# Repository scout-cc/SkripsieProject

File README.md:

# SkripsieProject
Designs and reports for personal final year engineering project

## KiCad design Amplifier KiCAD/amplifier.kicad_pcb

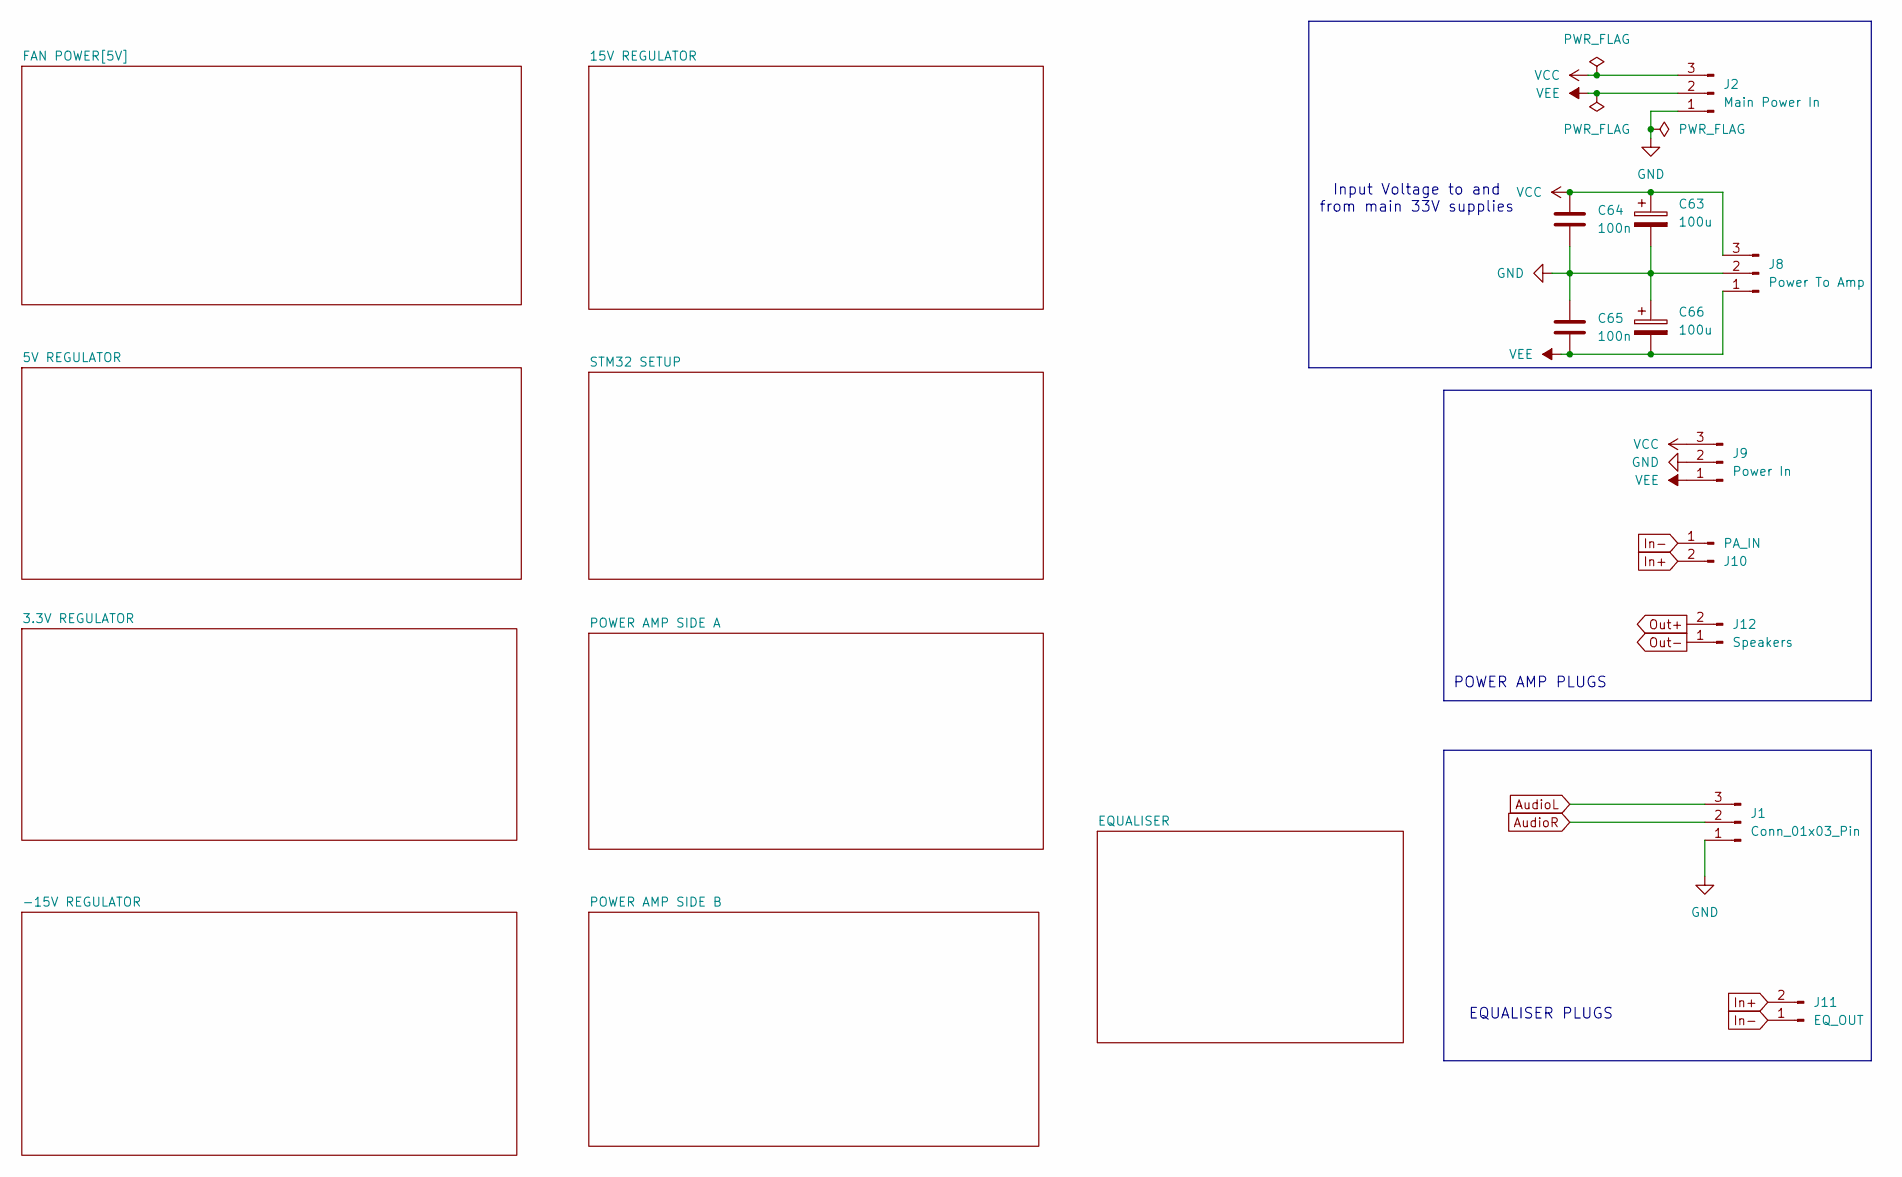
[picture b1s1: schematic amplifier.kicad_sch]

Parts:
C63, C66: 100u; CP_Radial_D6.3mm_P2.50mm
C64, C65: 100n; C_Rect_L7.2mm_W2.5mm_P5.00mm
J1: Conn_01x03_Pin; CUI_SJ1-3513
J2: Main Power In; PHOENIX_1829167
J8: Power To Amp; PHOENIX_1829167
J9: Power In; PHOENIX_1829167
J10: PA_IN; JST_PH_B3B-PH-K_1x03_P2.00mm_Vertical
J11: EQ_OUT; JST_PH_B3B-PH-K_1x03_P2.00mm_Vertical
J12: Speakers; PHOENIX_1757242

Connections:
AudioL: J1.3; also elsewhere on the board
AudioR: J1.2; also elsewhere on the board
GND: C63.2, C64.1, C65.2, C66.1, J1.1, J2.1, J8.2, J9.2; also elsewhere on the board
In+: J10.2, J11.2; also elsewhere on the board
In-: J10.1, J11.1; also elsewhere on the board
Out+: J12.2; also elsewhere on the board
Out-: J12.1; also elsewhere on the board
VCC: C63.1, C64.2, J2.3, J8.3, J9.3; also elsewhere on the board
VEE: C65.1, C66.2, J2.2, J8.1, J9.1; also elsewhere on the board

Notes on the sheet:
EQUALISER PLUGS
Input Voltage to and from main 33V supplies
POWER AMP PLUGS

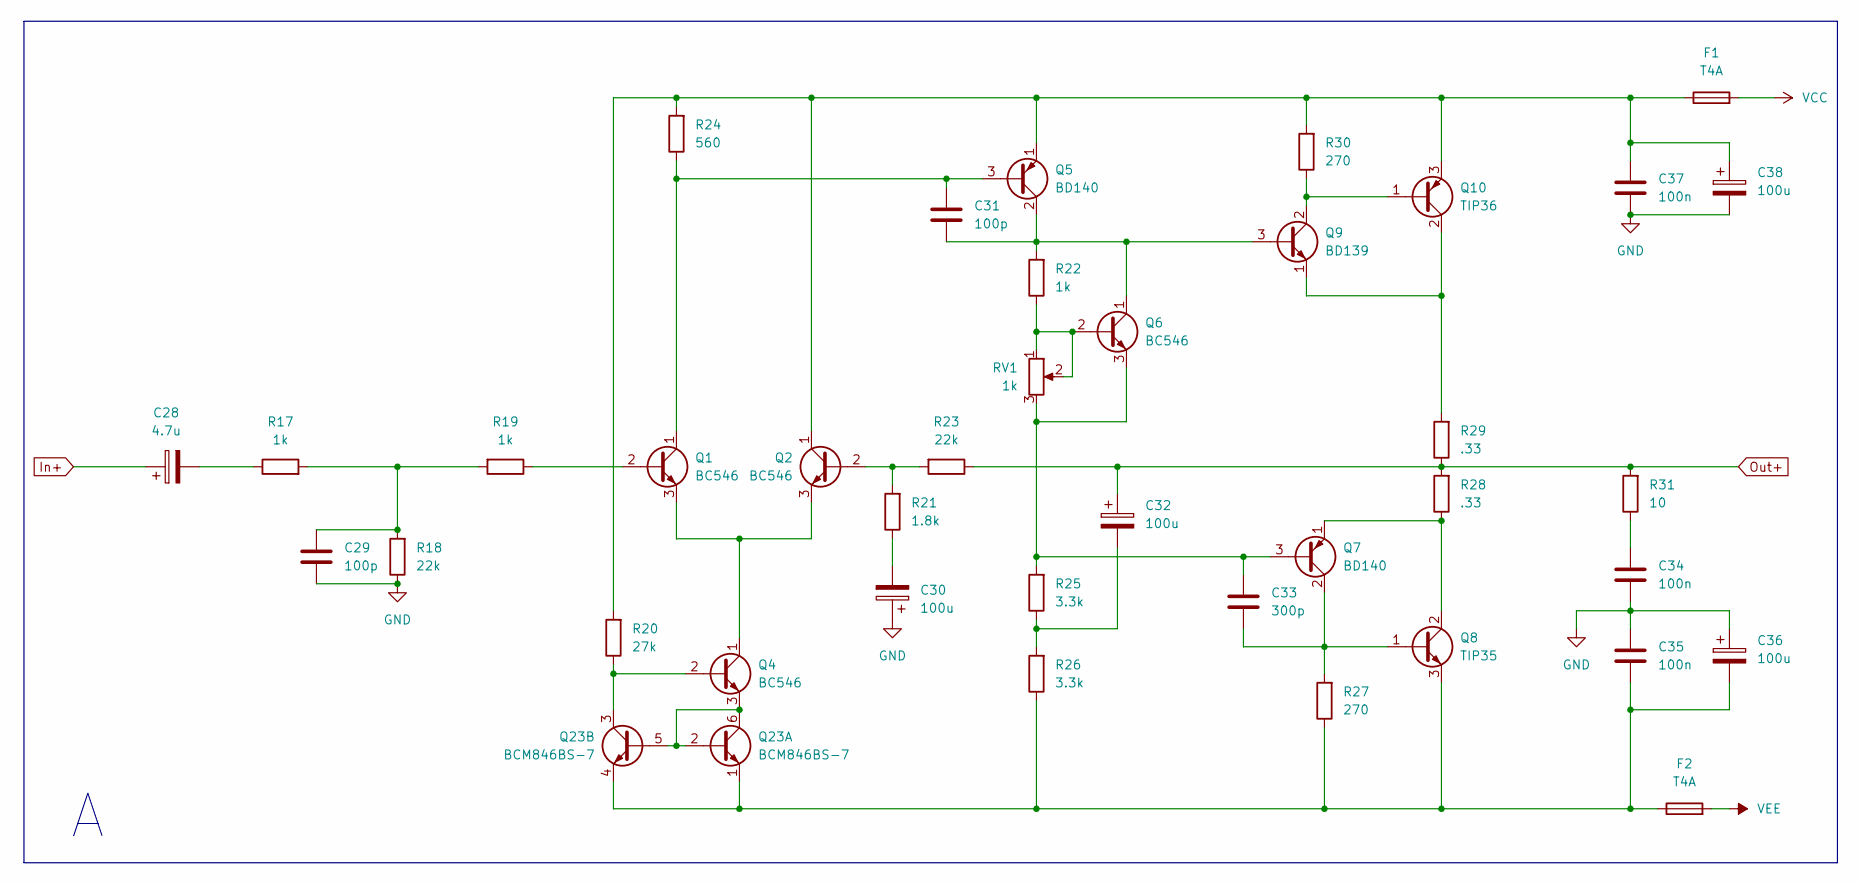
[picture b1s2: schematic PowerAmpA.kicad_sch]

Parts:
C28: 4.7u; GCJ31CC71H475KA01L
C29, C31: 100p; C0805C101J5GACTU
C30, C32, C36, C38: 100u; CP_Radial_D6.3mm_P2.50mm
C33: 300p; C0805C301J5GACTU
C34, C35, C37: 100n; C_Rect_L7.2mm_W2.5mm_P5.00mm
F1, F2: T4A; Fuseholder_Cylinder-5x20mm_Schurter_0031_8201_Horizontal_Op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
Q1, Q2, Q4, Q6: BC546; TO-92_Inline
Q5, Q7: BD140; TO-126-3_Vertical
Q8: TIP35; TO-247-3_Horizontal_TabDown
Q9: BD139; TO-126-3_Vertical
Q10: TIP36; TO-247-3_Horizontal_TabDown
Q23: BCM846BS-7; SOT-363_SC-70-6
R17, R19, R22: 1k; R_Axial_DIN0207_L6.3mm_D2.5mm_P10.16mm_Horizontal
R18, R23: 22k; R_Axial_DIN0207_L6.3mm_D2.5mm_P10.16mm_Horizontal
R20: 27k; R_Axial_DIN0207_L6.3mm_D2.5mm_P10.16mm_Horizontal
R21: 1.8k; R_Axial_DIN0207_L6.3mm_D2.5mm_P10.16mm_Horizontal
R24: 560; R_Axial_DIN0207_L6.3mm_D2.5mm_P10.16mm_Horizontal
R25, R26: 3.3k; R_Axial_DIN0207_L6.3mm_D2.5mm_P10.16mm_Horizontal
R27, R30: 270; R_Axial_DIN0207_L6.3mm_D2.5mm_P10.16mm_Horizontal
R28, R29: .33; R_Box_L26.0mm_W5.0mm_P20.00mm
R31: 10; R_Axial_DIN0411_L9.9mm_D3.6mm_P15.24mm_Horizontal
RV1: 1k; Potentiometer_Bourns_3296W_Vertical

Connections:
GND: C29.1, C30.1, C34.1, C35.2, C36.1, C37.1, C38.2, R18.1; also elsewhere on the board
In+: C28.1; also elsewhere on the board
unnamed: C28.2, R17.1
unnamed: C29.2, R17.2, R18.2, R19.2
unnamed: C30.2, R21.1
unnamed: C32.2, R25.1, R26.2
unnamed: C34.2, R31.1
unnamed: Q1.2 (B), R19.1
unnamed: C31.2, Q1.1 (C), Q5.3 (B), R24.1
unnamed: Q1.3 (E), Q2.3 (E), Q4.1 (C)
unnamed: Q2.2 (B), R21.2, R23.2
unnamed: C31.1, Q5.2 (C), Q6.1 (C), Q9.3 (B), R22.2
unnamed: Q6.2 (B), R22.1, RV1.1, RV1.2
unnamed: C33.2, Q6.3 (E), Q7.3 (B), R25.2, RV1.3
unnamed: C33.1, Q7.2 (C), Q8.1 (B), R27.2
unnamed: Q7.1 (E), Q8.2 (C), R28.1
unnamed: Q9.2 (C), Q10.1 (B), R30.1
unnamed: Q9.1 (E), Q10.2 (C), R29.2
unnamed: C37.2, C38.1, F1.1, Q2.1 (C), Q5.1 (E), Q10.3 (E), R20.2, R24.2, R30.2
unnamed: Q4.3 (E), Q23.2 (B1), Q23.5 (B2), Q23.6 (C1)
unnamed: C35.1, C36.2, F2.1, Q8.3 (E), Q23.1 (E1), Q23.4 (E2), R26.1, R27.1
unnamed: Q4.2 (B), Q23.3 (C2), R20.1
Out+: C32.1, R23.1, R28.2, R29.1, R31.2; also elsewhere on the board
VCC: F1.2; also elsewhere on the board
VEE: F2.2; also elsewhere on the board

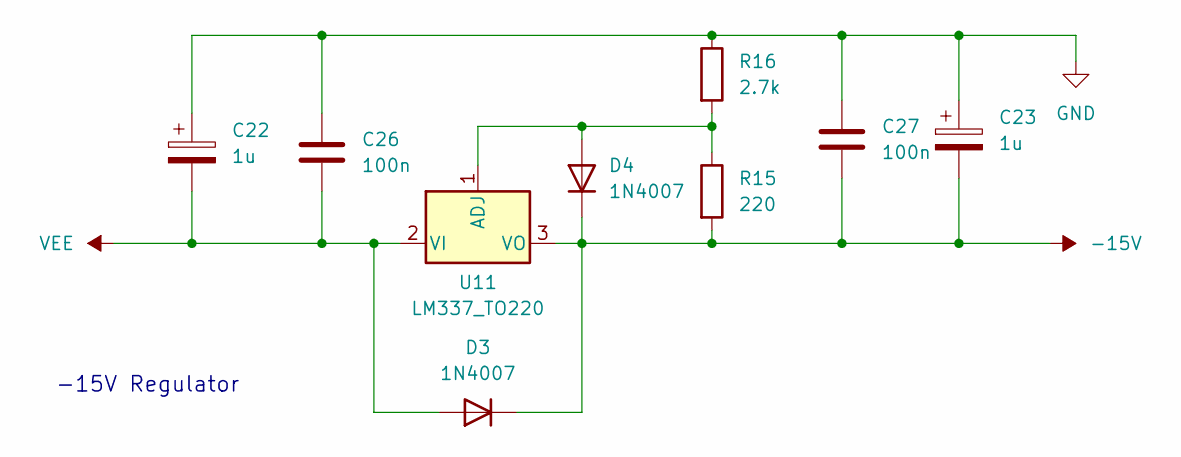
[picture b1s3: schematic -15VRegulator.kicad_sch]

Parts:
C22, C23: 1u; GJ821BR71H105KA12L
C26, C27: 100n; C_Rect_L7.2mm_W2.5mm_P5.00mm
D3, D4: 1N4007; D_DO-41_SOD81_P10.16mm_Horizontal
R15: 220; R_Axial_DIN0207_L6.3mm_D2.5mm_P10.16mm_Horizontal
R16: 2.7k; R_Axial_DIN0207_L6.3mm_D2.5mm_P10.16mm_Horizontal
U11: LM337_TO220; TO-220-3_Horizontal_TabDown

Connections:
-15V: C23.2, C27.2, D3.1 (K), D4.1 (K), R15.2, U11.3 (VO); also elsewhere on the board
GND: C22.1, C23.1, C26.1, C27.1, R16.1; also elsewhere on the board
unnamed: D4.2 (A), R15.1, R16.2, U11.1 (ADJ)
VEE: C22.2, C26.2, D3.2 (A), U11.2 (VI); also elsewhere on the board

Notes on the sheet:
-15V Regulator

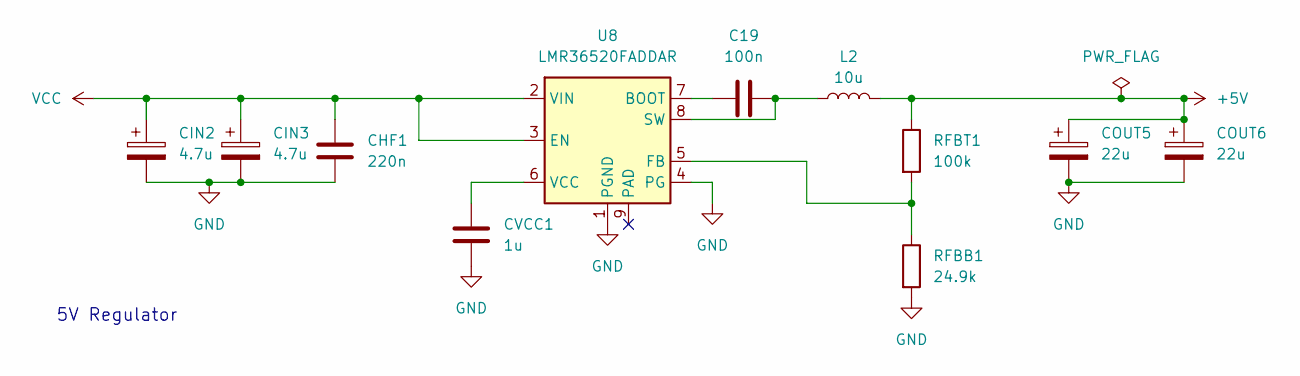
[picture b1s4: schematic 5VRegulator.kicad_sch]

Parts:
C19: 100n; C_Rect_L7.2mm_W2.5mm_P5.00mm
CHF1: 220n; C_Rect_L7.2mm_W2.5mm_P5.00mm
CIN2, CIN3: 4.7u; GCJ31CC71H475KA01L
COUT5, COUT6: 22u; G-32_MUR
CVCC1: 1u; GJ821BR71H105KA12L
L2: 10u; IND_SRP1038A_BRN
RFBB1: 24.9k; R_0805_2012Metric
RFBT1: 100k; R_Axial_DIN0207_L6.3mm_D2.5mm_P10.16mm_Horizontal
U8: LMR36520FADDAR; Texas_HTSOP-8-1EP_3.9x4.9mm_P1.27mm_EP2.95x4.9mm_Mask2.4x3.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

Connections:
+5V: COUT5.1, COUT6.1, L2.2, RFBT1.1; also elsewhere on the board
GND: CHF1.2, CIN2.2, CIN3.2, COUT5.2, COUT6.2, CVCC1.2, RFBB1.2, U8.1 (PGND), U8.4 (PG); also elsewhere on the board
unnamed: C19.1, U8.7 (BOOT)
unnamed: RFBB1.1, RFBT1.2, U8.5 (FB)
unnamed: C19.2, L2.1, U8.8 (SW)
unnamed: CVCC1.1, U8.6 (VCC)
VCC: CHF1.1, CIN2.1, CIN3.1, U8.2 (VIN), U8.3 (EN); also elsewhere on the board

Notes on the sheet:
5V Regulator

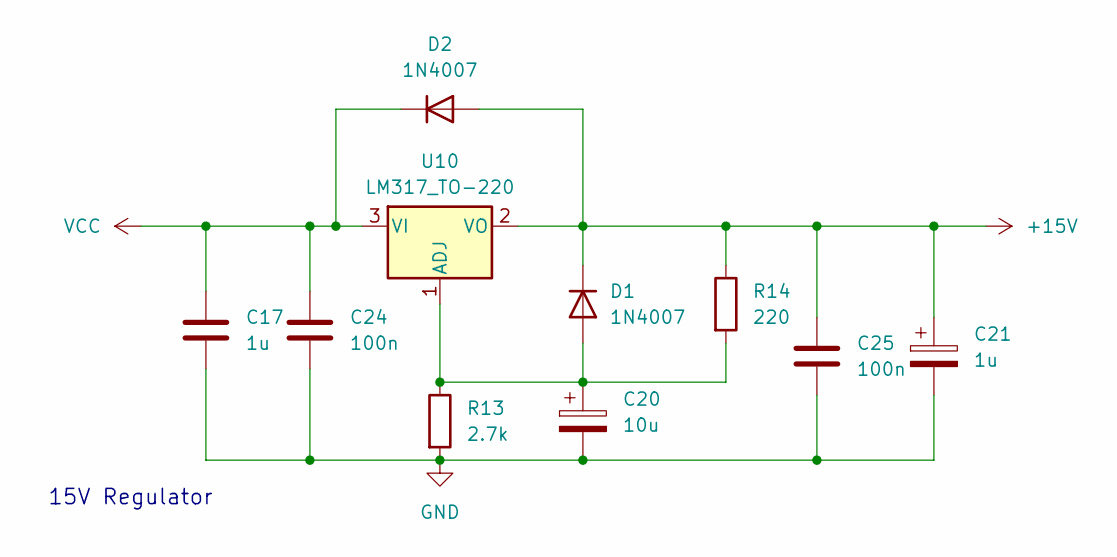
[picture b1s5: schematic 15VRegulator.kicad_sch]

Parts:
C17, C21: 1u; GJ821BR71H105KA12L
C20: 10u; CAP_GCM32_MUR
C24, C25: 100n; C_Rect_L7.2mm_W2.5mm_P5.00mm
D1, D2: 1N4007; D_DO-41_SOD81_P10.16mm_Horizontal
R13: 2.7k; R_Axial_DIN0207_L6.3mm_D2.5mm_P10.16mm_Horizontal
R14: 220; R_Axial_DIN0207_L6.3mm_D2.5mm_P10.16mm_Horizontal
U10: LM317_TO-220; TO-220-3_Horizontal_TabDown

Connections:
+15V: C21.1, C25.1, D1.1 (K), D2.2 (A), R14.1, U10.2 (VO); also elsewhere on the board
GND: C17.2, C20.2, C21.2, C24.2, C25.2, R13.2; also elsewhere on the board
unnamed: C20.1, D1.2 (A), R13.1, R14.2, U10.1 (ADJ)
VCC: C17.1, C24.1, D2.1 (K), U10.3 (VI); also elsewhere on the board

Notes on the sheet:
15V Regulator

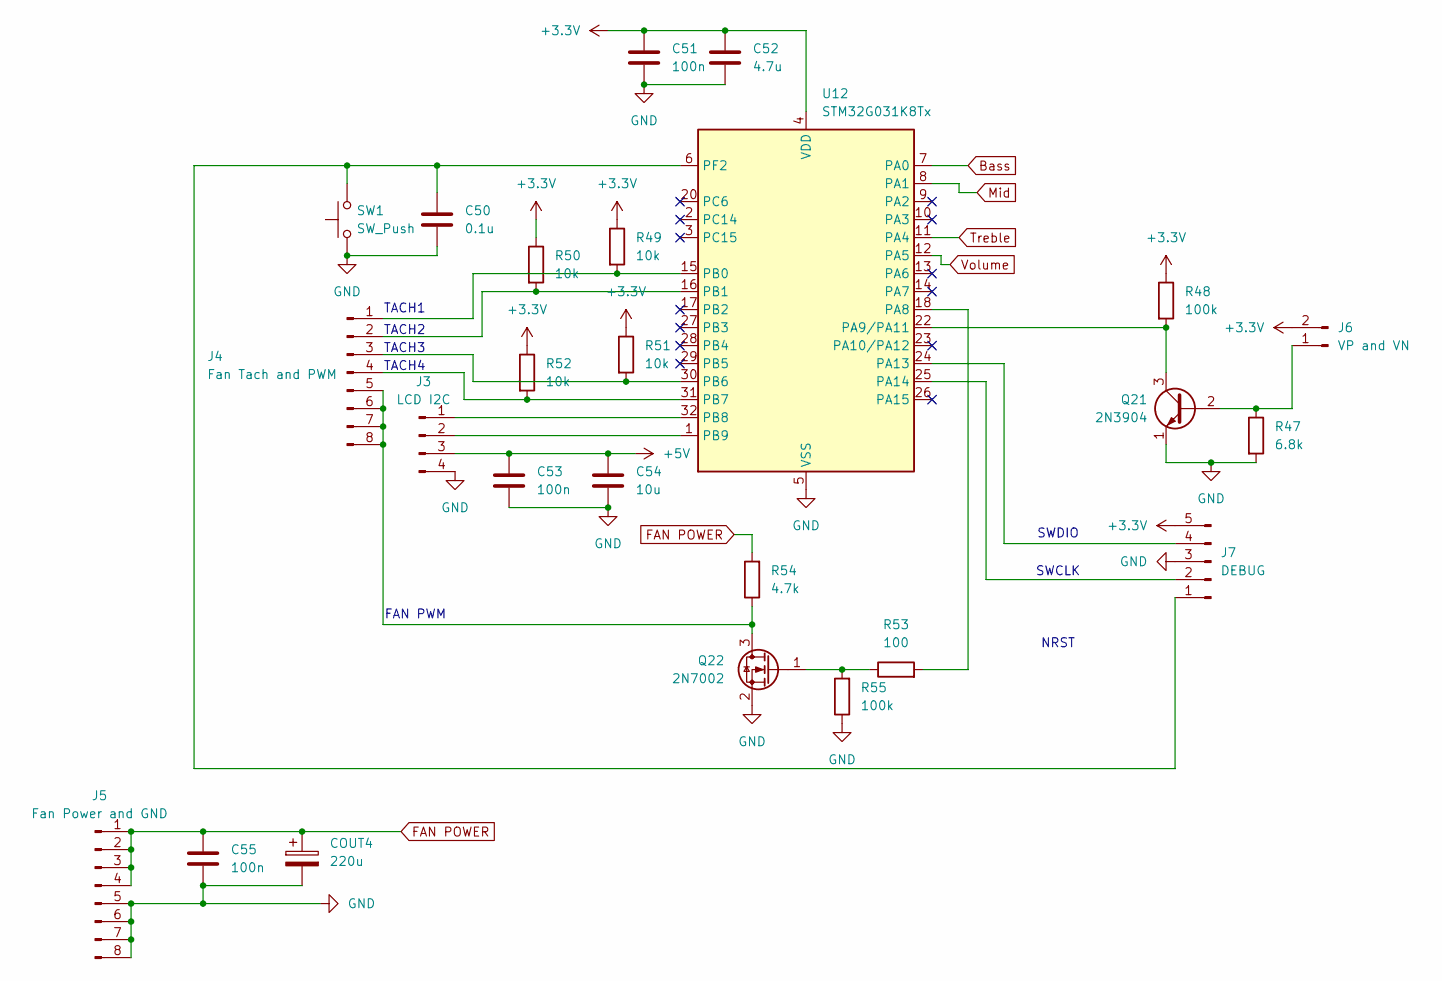
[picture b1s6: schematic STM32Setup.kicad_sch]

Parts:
C50: 0.1u; C_Rect_L7.2mm_W2.5mm_P5.00mm
C51, C53, C55: 100n; C_Rect_L7.2mm_W2.5mm_P5.00mm
C52: 4.7u; GCJ31CC71H475KA01L
C54: 10u; CAP_GCM32_MUR
COUT4: 220u; CP_Radial_D6.3mm_P2.50mm
J3: LCD I2C; PinHeader_1x04_P2.00mm_Vertical
J4: Fan Tach and PWM; JST_XH_B8B-XH-A_1x08_P2.50mm_Vertical
J5: Fan Power and GND; Molex_Micro-Fit_3.0_43045-0812_2x04_P3.00mm_Vertical
J6: VP and VN; JST_PH_B2B-PH-K_1x02_P2.00mm_Vertical
J7: DEBUG; JST_PH_B5B-PH-K_1x05_P2.00mm_Vertical
Q21: 2N3904; TO-92_Inline
Q22: 2N7002; SOT-23
R47: 6.8k; R_Axial_DIN0207_L6.3mm_D2.5mm_P10.16mm_Horizontal
R48, R55: 100k; R_Axial_DIN0207_L6.3mm_D2.5mm_P10.16mm_Horizontal
R49, R50, R51, R52: 10k; R_Axial_DIN0207_L6.3mm_D2.5mm_P10.16mm_Horizontal
R53: 100; R_Axial_DIN0207_L6.3mm_D2.5mm_P10.16mm_Horizontal
R54: 4.7k; R_Axial_DIN0207_L6.3mm_D2.5mm_P10.16mm_Horizontal
SW1: SW_Push; SW_PUSH_6mm_H5mm
U12: STM32G031K8Tx; LQFP-32_7x7mm_P0.8mm

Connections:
+3.3V: C51.1, C52.1, J6.2, J7.5, R48.1, R49.1, R50.1, R51.1, R52.1, U12.4 (VDD); also elsewhere on the board
+5V: C53.1, C54.1, J3.3; also elsewhere on the board
Bass: U12.7 (PA0); also elsewhere on the board
FAN POWER: C55.1, COUT4.1, J5.1, J5.2, J5.3, J5.4, R54.2; also elsewhere on the board
GND: C50.2, C51.2, C52.2, C53.2, C54.2, C55.2, COUT4.2, J3.4, J5.5, J5.6, J5.7, J5.8, J7.3, Q21.1 (E), Q22.2 (S), R47.2, R55.1, SW1.1, U12.5 (VSS); also elsewhere on the board
Mid: U12.8 (PA1); also elsewhere on the board
unnamed: J3.1, U12.32 (PB8)
unnamed: J3.2, U12.1 (PB9)
unnamed: J4.1, R49.2, U12.15 (PB0)
unnamed: J4.2, R50.2, U12.16 (PB1)
unnamed: J4.3, R51.2, U12.30 (PB6)
unnamed: J4.4, R52.2, U12.31 (PB7)
unnamed: J4.5, J4.6, J4.7, J4.8, Q22.3 (D), R54.1
unnamed: J6.1, Q21.2 (B), R47.1
unnamed: C50.1, J7.1, SW1.2, U12.6 (PF2)
unnamed: J7.2, U12.25 (PA14)
unnamed: J7.4, U12.24 (PA13)
unnamed: Q21.3 (C), R48.2, U12.22 (PA9/PA11)
unnamed: Q22.1 (G), R53.1, R55.2
unnamed: R53.2, U12.18 (PA8)
Treble: U12.11 (PA4); also elsewhere on the board
Volume: U12.12 (PA5); also elsewhere on the board

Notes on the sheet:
TACH2
TACH1
NRST
SWCLK
TACH3
FAN PWM
TACH4
SWDIO

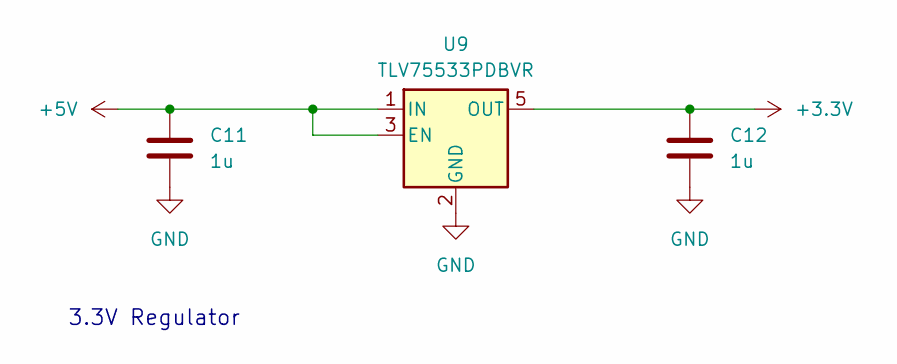
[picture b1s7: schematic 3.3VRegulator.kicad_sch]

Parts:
C11, C12: 1u; GJ821BR71H105KA12L
U9: TLV75533PDBVR; SOT-23-5

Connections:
+3.3V: C12.1, U9.5 (OUT); also elsewhere on the board
+5V: C11.1, U9.1 (IN), U9.3 (EN); also elsewhere on the board
GND: C11.2, C12.2, U9.2 (GND); also elsewhere on the board

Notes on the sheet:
3.3V Regulator

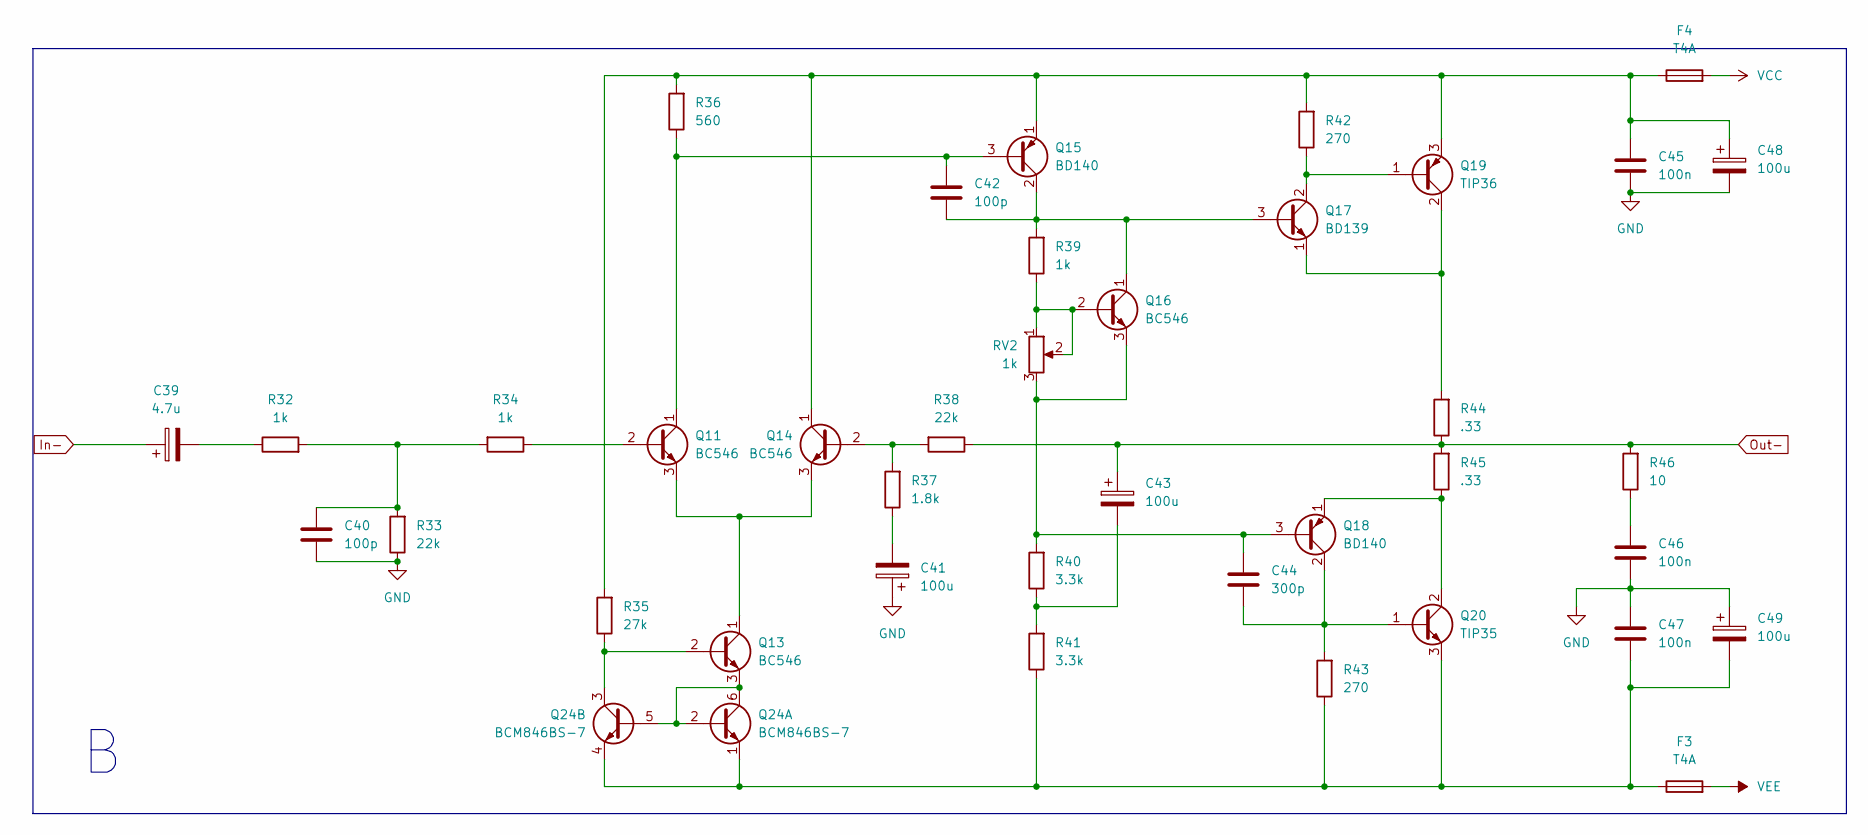
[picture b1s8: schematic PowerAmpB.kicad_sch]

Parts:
C39: 4.7u; GCJ31CC71H475KA01L
C40, C42: 100p; C0805C101J5GACTU
C41, C43, C48, C49: 100u; CP_Radial_D6.3mm_P2.50mm
C44: 300p; C0805C301J5GACTU
C45, C46, C47: 100n; C_Rect_L7.2mm_W2.5mm_P5.00mm
F3, F4: T4A; Fuseholder_Cylinder-5x20mm_Schurter_0031_8201_Horizontal_Op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
Q11, Q13, Q14, Q16: BC546; TO-92_Inline
Q15, Q18: BD140; TO-126-3_Vertical
Q17: BD139; TO-126-3_Vertical
Q19: TIP36; TO-247-3_Horizontal_TabDown
Q20: TIP35; TO-247-3_Horizontal_TabDown
Q24: BCM846BS-7; SOT-363_SC-70-6
R32, R34, R39: 1k; R_Axial_DIN0207_L6.3mm_D2.5mm_P10.16mm_Horizontal
R33, R38: 22k; R_Axial_DIN0207_L6.3mm_D2.5mm_P10.16mm_Horizontal
R35: 27k; R_Axial_DIN0207_L6.3mm_D2.5mm_P10.16mm_Horizontal
R36: 560; R_Axial_DIN0207_L6.3mm_D2.5mm_P10.16mm_Horizontal
R37: 1.8k; R_Axial_DIN0207_L6.3mm_D2.5mm_P10.16mm_Horizontal
R40, R41: 3.3k; R_Axial_DIN0207_L6.3mm_D2.5mm_P10.16mm_Horizontal
R42, R43: 270; R_Axial_DIN0207_L6.3mm_D2.5mm_P10.16mm_Horizontal
R44, R45: .33; R_Box_L26.0mm_W5.0mm_P20.00mm
R46: 10; R_Axial_DIN0411_L9.9mm_D3.6mm_P15.24mm_Horizontal
RV2: 1k; Potentiometer_Bourns_3296W_Vertical

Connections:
GND: C40.1, C41.1, C45.1, C46.1, C47.2, C48.2, C49.1, R33.1; also elsewhere on the board
In-: C39.1; also elsewhere on the board
unnamed: C39.2, R32.1
unnamed: C40.2, R32.2, R33.2, R34.2
unnamed: C41.2, R37.1
unnamed: C43.2, R40.1, R41.2
unnamed: C46.2, R46.1
unnamed: Q11.2 (B), R34.1
unnamed: C42.2, Q11.1 (C), Q15.3 (B), R36.1
unnamed: Q11.3 (E), Q13.1 (C), Q14.3 (E)
unnamed: Q13.2 (B), Q24.3 (C2), R35.1
unnamed: Q13.3 (E), Q24.2 (B1), Q24.5 (B2), Q24.6 (C1)
unnamed: Q14.2 (B), R37.2, R38.2
unnamed: C45.2, C48.1, F4.1, Q14.1 (C), Q15.1 (E), Q19.3 (E), R35.2, R36.2, R42.2
unnamed: C42.1, Q15.2 (C), Q16.1 (C), Q17.3 (B), R39.2
unnamed: Q16.2 (B), R39.1, RV2.1, RV2.2
unnamed: C44.2, Q16.3 (E), Q18.3 (B), R40.2, RV2.3
unnamed: Q17.2 (C), Q19.1 (B), R42.1
unnamed: Q17.1 (E), Q19.2 (C), R44.2
unnamed: C44.1, Q18.2 (C), Q20.1 (B), R43.2
unnamed: Q18.1 (E), Q20.2 (C), R45.1
unnamed: C47.1, C49.2, F3.1, Q20.3 (E), Q24.1 (E1), Q24.4 (E2), R41.1, R43.1
Out-: C43.1, R38.1, R44.1, R45.2, R46.2; also elsewhere on the board
VCC: F4.2; also elsewhere on the board
VEE: F3.2; also elsewhere on the board

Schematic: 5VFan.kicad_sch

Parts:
C18: 100n; C_Rect_L7.2mm_W2.5mm_P5.00mm
CHF2: 220n; C_Rect_L7.2mm_W2.5mm_P5.00mm
CIN1, CIN4: 4.7u; GCJ31CC71H475KA01L
COUT1, COUT2: 22u; G-32_MUR
CVCC2: 1u; GJ821BR71H105KA12L
L1: 10u; IND_SRP1038A_BRN
RFBB2: 24.9k; R_Axial_DIN0207_L6.3mm_D2.5mm_P10.16mm_Horizontal
RFBT2: 100k; R_Axial_DIN0207_L6.3mm_D2.5mm_P10.16mm_Horizontal
U7: LMR36520FADDAR; Texas_HTSOP-8-1EP_3.9x4.9mm_P1.27mm_EP2.95x4.9mm_Mask2.4x3.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

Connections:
FAN POWER: COUT1.1, COUT2.1, L1.2, RFBT2.1; also elsewhere on the board
GND: CHF2.2, CIN1.2, CIN4.2, COUT1.2, COUT2.2, CVCC2.2, RFBB2.2, U7.1 (PGND), U7.4 (PG); also elsewhere on the board
unnamed: C18.1, U7.7 (BOOT)
unnamed: RFBB2.1, RFBT2.2, U7.5 (FB)
unnamed: C18.2, L1.1, U7.8 (SW)
unnamed: CVCC2.1, U7.6 (VCC)
VCC: CHF2.1, CIN1.1, CIN4.1, U7.2 (VIN), U7.3 (EN); also elsewhere on the board

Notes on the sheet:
FAN POWER[5V]

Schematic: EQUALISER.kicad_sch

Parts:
C1, C2: 4.7u; GCJ31CC71H475KA01L
C3, C4, C5: 2.2u; ECEA1HN2R2U
C6, C13, C14, C16: 22n; C_Rect_L7.2mm_W2.5mm_P5.00mm
C7, C8, C10, C15, C56, C57, C58, C59, C60, C61, C62: 100n; C_Rect_L7.2mm_W2.5mm_P5.00mm
C9: 1.5n; C_Rect_L7.2mm_W2.5mm_P5.00mm
R1, R2, R11, R12: 10k; R_Axial_DIN0207_L6.3mm_D2.5mm_P10.16mm_Horizontal
R3, R5, R8, R10: 470; R_Axial_DIN0207_L6.3mm_D2.5mm_P10.16mm_Horizontal
R4: 3.3k; R_Axial_DIN0207_L6.3mm_D2.5mm_P10.16mm_Horizontal
R6, R7, R9: 100k; R_Axial_DIN0207_L6.3mm_D2.5mm_P10.16mm_Horizontal
RV5, RV6, RV7, RV8: 10k; Bourns_PTD902_Dual_Horizontal
U1, U2, U3, U4, U5, U6: TL081; DIP-8_W7.62mm_LongPads

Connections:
+3.3V: RV5.6, RV6.6, RV7.6, RV8.6; also elsewhere on the board
+15V: C56.2, C57.2, C58.2, C59.2, U1.7 (V+), U2.7 (V+), U3.7 (V+), U4.7 (V+), U5.7 (V+), U6.7 (V+); also elsewhere on the board
-15V: U1.4 (V-), U2.4 (V-), U3.4 (V-), U4.4 (V-), U5.4 (V-), U6.4 (V-); also elsewhere on the board
AudioL: C1.1; also elsewhere on the board
AudioR: C2.1; also elsewhere on the board
Bass: RV5.5; also elsewhere on the board
GND: C56.1, C57.1, C58.1, C60.2, C61.2, C62.2, R6.1, R7.1, R9.1, RV5.4, RV6.4, RV7.4, RV8.4, U1.3 (+), U6.3 (+); also elsewhere on the board
In+: C59.1, R11.1, RV8.1, U3.6; also elsewhere on the board
In-: R12.2, U6.6; also elsewhere on the board
Mid: RV6.5; also elsewhere on the board
unnamed: C1.2, R1.1
unnamed: C2.2, R2.1
unnamed: C3.1, C4.1, C5.1, C6.1, R5.1
unnamed: C3.2, C4.2, C5.2, RV5.2
unnamed: C7.1, C8.1, C10.1, C15.1, RV6.2
unnamed: C7.2, C8.2, C9.1, C10.2, C15.2, R8.1
unnamed: C13.1, RV7.2
unnamed: C13.2, C14.1, C16.1, R10.1
unnamed: R3.2, R4.1, U1.6
unnamed: R1.2, R2.2, R3.1, U1.2 (-)
unnamed: C6.2, R6.2, U2.3 (+)
unnamed: C60.1, R5.2, U2.2 (-), U2.6
unnamed: R4.2, RV5.1, RV6.1, RV7.1, U3.3 (+)
unnamed: RV5.3, RV6.3, RV7.3, RV8.2, U3.2 (-)
unnamed: C9.2, R7.2, U4.3 (+)
unnamed: C61.1, R8.2, U4.2 (-), U4.6
unnamed: C14.2, C16.2, R9.2, U5.3 (+)
unnamed: C62.1, R10.2, U5.2 (-), U5.6
unnamed: R11.2, R12.1, U6.2 (-)
Treble: RV7.5; also elsewhere on the board
Volume: RV8.5; also elsewhere on the board

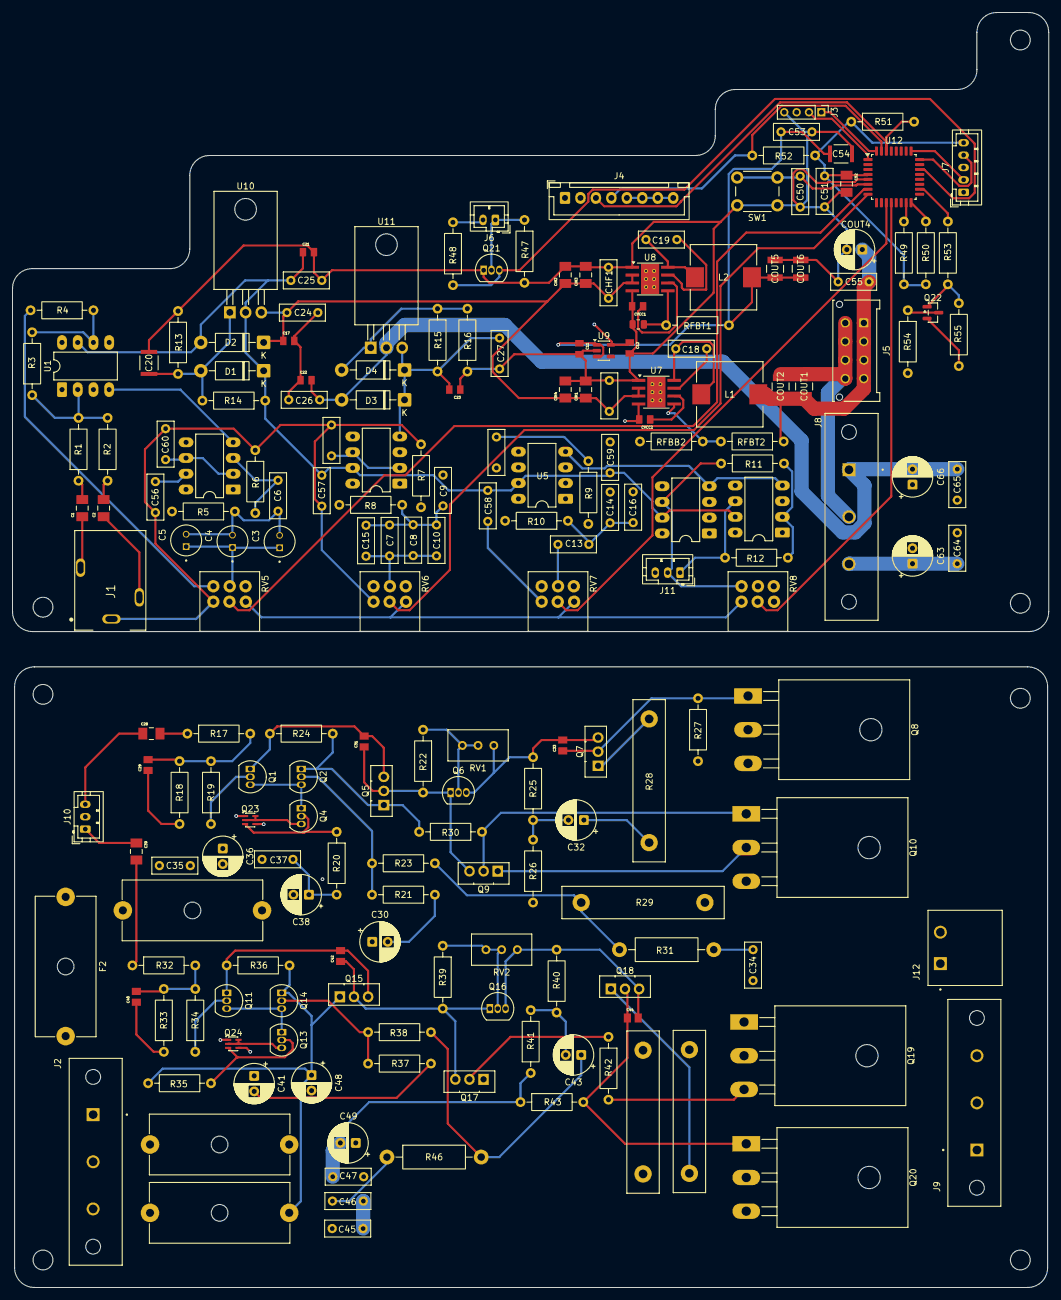
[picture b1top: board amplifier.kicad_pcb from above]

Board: 4 copper layers, 167.5 x 206.1 mm, 201 parts (0 on the bottom side), 101 nets.

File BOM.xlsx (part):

Part Number | Description | Manufacturer | Package | Reference | Qty | Value | Price(ZAR) | Price Total | URL | KiCAD Assinged
GCJ31CC71H475KA01L | 4.7 µF ±10% 50 V X7S ceramic capacitor | Murata Electronics | Capacitor_SMD:C_1206_3216Metric | C1,C2,C28,C39,C52,CIN1,CIN2,CIN3,CIN4 | 10 | 4.7u | 6.34293 | 63.429299999999998 | https://www.digikey.co.za/en/products/detail/murata-electron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
ECE-A1HN2R2U | 2.2 µF 50 V radial aluminium electrolytic capacitor | Panasonic Industry | Capacitor_THT:CP_Radial_D5.0mm_P2.00mm | C3,C4,C5 | 10 | 2.2u | 4.2777900000000004 | 42.777900000000002 | https://www.digikey.co.za/en/products/detail/panasonic-indus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
N/A | 22 nF capacitor (lab stock; type and voltage unknown) | N/A | Capacitor_THT:C_Rect_L7.2mm_W2.5mm_P5.00mm (verify dimensions) | C6,C13,C14,C16 | 4 | 22n | 0 | 0 | Labs
N/A | 100 nF capacitor (lab stock; type and voltage unknown) | N/A | Capacitor_THT:C_Rect_L7.2mm_W2.5mm_P5.00mm (verify dimensions) | C7,C8,C10,C15,C18,C19,C24,C25,C26,C27,C34,C35,C37,C45,C46,C47,C51,C53,C55,C56,C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 | 26 | 100n | 0 | 0 | Labs
N/A | 1.5 nF capacitor (lab stock; type and voltage unknown) | N/A | Capacitor_THT:C_Rect_L7.2mm_W2.5mm_P5.00mm (verify dimensions) | C9 | 1 | 1.5n | 0 | 0 | Labs
GJ821BR71H105KA12L | 1 µF ±10% 50 V X7R ceramic capacitor | Murata Electronics | Capacitor_SMD:C_0805_2012Metric | C11,C12,C17,C21,C22,C23,CVCC1,CVCC2 | 10 | 1u | 3.6713600000000004 | 36.713600000000007 | https://www.digikey.co.za/en/products/detail/murata-electron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
GCM32EC71H106KA03L | 10 µF ±10% 50 V X7S ceramic capacitor | Murata Electronics | Capacitor_SMD:C_1210_3225Metric | C20,C54 | 10 | 10u | 9.3259100000000004 | 93.259100000000004 | https://www.digikey.co.za/en/products/detail/murata-electron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
C0805C101J5GACTU | 100 pF ±5% 50 V C0G/NP0 ceramic capacitor | KEMET | Capacitor_SMD:C_0805_2012Metric | C29,C31,C40,C42 | 10 | 100p | 1.22925 | 12.2925 | https://www.digikey.co.za/en/products?keywords=C0805C101J5GACTU
N/A | 100 µF electrolytic capacitor (lab stock; voltage and dimensions unknown) | N/A | N/A (measure can diameter and lead pitch) | C30,C32,C36,C38,C41,C43,C48,C49 | 8 | 100u | 0 | 0 | Labs
C0805C301J5GACTU | 300 pF ±5% 50 V C0G/NP0 ceramic capacitor | KEMET | Capacitor_SMD:C_0805_2012Metric | C33,C44 | 10 | 300p | 3.0649299999999999 | 30.6493 | https://www.digikey.co.za/en/products?keywords=C0805C301J5GACTU
N/A | 0.1 µF capacitor (lab stock; type and voltage unknown) | N/A | Capacitor_THT:C_Rect_L7.2mm_W2.5mm_P5.00mm (verify dimensions) | C50 | 1 | 0.1u | 0 | 0 | Labs
N/A | 220 nF capacitor (lab stock; type and voltage unknown) | N/A | Capacitor_THT:C_Rect_L7.2mm_W2.5mm_P5.00mm (verify dimensions) | CHF1,CHF2 | 2 | 220n | 0 | 0 | Labs
N/A | 220 µF electrolytic capacitor (lab stock; voltage and dimensions unknown) | N/A | N/A (measure can diameter and lead pitch) | COUT4 | 1 | 220u | 0 | 0 | Labs
GRM32ER71E226KE15L | 22 µF ±10% 25 V X7R ceramic capacitor | Murata Electronics | Capacitor_SMD:C_1210_3225Metric | COUT5,COUT6,COUT1,COUT2 | 10 | 22u | 7.8180300000000003 | 78.180300000000003 | https://www.digikey.co.za/en/products?keywords=GRM32ER71E226KE15L
1N4007 | 1 A 1000 V general-purpose rectifier diode (lab stock) | N/A | Diode_THT:D_DO-41_SOD81_P10.16mm_Horizontal | D1,D2,D3,D4 | 4 | 1N4007 | 0 | 0 | Labs?
0477004.MXP | 4 A time-delay ceramic cartridge fuse, 5 × 20 mm | Littelfuse | 5 × 20 mm cartridge (installed in separate holder) | F1,F2,F3,F4 | 5 | T4A | 32.255520000000004 | 161.27760000000001 | https://www.digikey.co.za/en/products?keywords=0477004.MXP
SJ1-3513 | 3.5 mm stereo TRS phone jack, panel mount, right-angle | Same Sky (formerly CUI Devices) | N/A (panel-mount solder-lug connector) | J1 | 1 | Conn_01x03_Pin | 30.321500000000004 | 30.321500000000004 | https://www.digikey.co.za/en/products/detail/same-sky-former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
1829167 | 3-position 7.62 mm vertical pluggable terminal-block header | Phoenix Contact | TerminalBlock_Phoenix:PhoenixContact_GMSTBV_2,5_3-G-7,62_1x03_P7.62mm_Vertical | J2 | 1 | Main Power In | 54.742600000000003 | 54.742600000000003 | https://www.digikey.co.za/en/products/detail/phoenix-contact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
2SH-C-04-TS | 4-position 2.00 mm vertical shrouded through-hole header | Adam Tech | Connector_PinHeader_2.00mm:PinHeader_1x04_P2.00mm_Vertical | J3 | 1 | LCD I2C | 1.9668000000000001 | 1.9668000000000001 | https://www.digikey.co.za/en/products/detail/adam-tech/2SH-C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
B8B-XH-A | 8-position 2.50 mm vertical JST XH through-hole header | JST Sales America Inc. | Connector_JST:JST_XH_B8B-XH-A_1x08_P2.50mm_Vertical | J4 | 1 | Fan Tach and PWM | 4.9169999999999998 | 4.9169999999999998 | https://www.digikey.co.za/en/products/detail/jst-sales-ameri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
0430450812 | 8-position 3.00 mm dual-row vertical Micro-Fit 3.0 header | Molex | Connector_Molex:Molex_Micro-Fit_3.0_43045-0812_2x04_P3.00mm_Vertical | J5 | 1 | Fan Power and GND | 23.929400000000001 | 23.929400000000001 | https://www.digikey.co.za/en/products?keywords=43045-0812
B2B-PH-K-S | 2-position 2.00 mm vertical JST PH through-hole header | JST Sales America Inc. | Connector_JST:JST_PH_B2B-PH-K_1x02_P2.00mm_Vertical | J6 | 1 | VP and VN | 1.8029000000000002 | 1.8029000000000002 | https://www.digikey.co.za/en/products?keywords=B2B-PH-K-S%28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
B5B-PH-K-S | 5-position 2.00 mm vertical JST PH through-hole header | JST Sales America Inc. | Connector_JST:JST_PH_B5B-PH-K_1x05_P2.00mm_Vertical | J7 | 1 | DEBUG | 3.9336000000000002 | 3.9336000000000002 | https://www.digikey.co.za/en/products?keywords=B5B-PH-K-S%28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
1829167 | 3-position 7.62 mm vertical pluggable terminal-block header | Phoenix Contact | TerminalBlock_Phoenix:PhoenixContact_GMSTBV_2,5_3-G-7,62_1x03_P7.62mm_Vertical | J8 | 1 | Power To Amp | 54.742600000000003 | 54.742600000000003 | https://www.digikey.co.za/en/products/detail/phoenix-contact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
1829167 | 3-position 7.62 mm vertical pluggable terminal-block header | Phoenix Contact | TerminalBlock_Phoenix:PhoenixContact_GMSTBV_2,5_3-G-7,62_1x03_P7.62mm_Vertical | J9 | 1 | Power In | 54.742600000000003 | 54.742600000000003 | https://www.digikey.co.za/en/products/detail/phoenix-contact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
B3B-PH-K-S | 3-position 2.00 mm vertical JST PH through-hole header | JST Sales America Inc. | Connector_JST:JST_PH_B3B-PH-K_1x03_P2.00mm_Vertical | J10 | 1 | PA_IN | 2.6224000000000003 | 2.6224000000000003 | https://www.digikey.co.za/en/products?keywords=B3B-PH-K-S%28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
B3B-PH-K-S | 3-position 2.00 mm vertical JST PH through-hole header | JST Sales America Inc. | Connector_JST:JST_PH_B3B-PH-K_1x03_P2.00mm_Vertical | J11 | 1 | EQ_OUT | 2.6224000000000003 | 2.6224000000000003 | https://www.digikey.co.za/en/products?keywords=B3B-PH-K-S%28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
1757242 | 2-position 5.08 mm right-angle pluggable terminal-block header | Phoenix Contact | TerminalBlock_Phoenix:PhoenixContact_MSTBA_2,5_2-G-5,08_1x02_P5.08mm_Horizontal | J12 | 1 | Speakers | 0 | 0 | https://www.digikey.co.za/en/products/detail/phoenix-contact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
SRP1038A-100M | 10 µH shielded SMD power inductor | Bourns | Inductor_SMD:L_Bourns-SRP1038A | L1, L2 | 1 | 10u | 17.537300000000002 | 17.537300000000002 | https://www.digikey.co.za/en/products/detail/bourns-inc/SRP1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
BC546 | NPN small-signal transistor (lab stock; exact suffix unknown) | N/A | Package_TO_SOT_THT:TO-92_Inline | Q1,Q2,Q4,Q6,Q11,Q13,Q14,Q16 | 8 | BC546 | 0 | 0 | Labs?
BCM846BS-7 | Dual matched NPN transistor, 65 V | Diodes Incorporated | Package_TO_SOT_SMD:SOT-363_SC-70-6 | Q3,Q12 | 10 | BCM846BS-7 | 2.4748899999999998 | 24.748899999999999 | https://www.digikey.co.za/en/products/detail/diodes-incorpor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
BD140 | PNP medium-power transistor, TO-126 | STMicroelectronics | Package_TO_SOT_THT:TO-126-3_Vertical | Q5,Q7,Q15,Q18 | 8 | BD140 | 29.665900000000001 | 237.3272 | https://www.digikey.co.za/en/products/detail/stmicroelectron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
TIP35C | NPN power transistor, TO-247-3 | STMicroelectronics | Package_TO_SOT_THT:TO-247-3_Vertical | Q8,Q20 | 4 | TIP35 | 63.757100000000001 | 255.0284 | https://www.digikey.co.za/en/products/detail/stmicroelectron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
